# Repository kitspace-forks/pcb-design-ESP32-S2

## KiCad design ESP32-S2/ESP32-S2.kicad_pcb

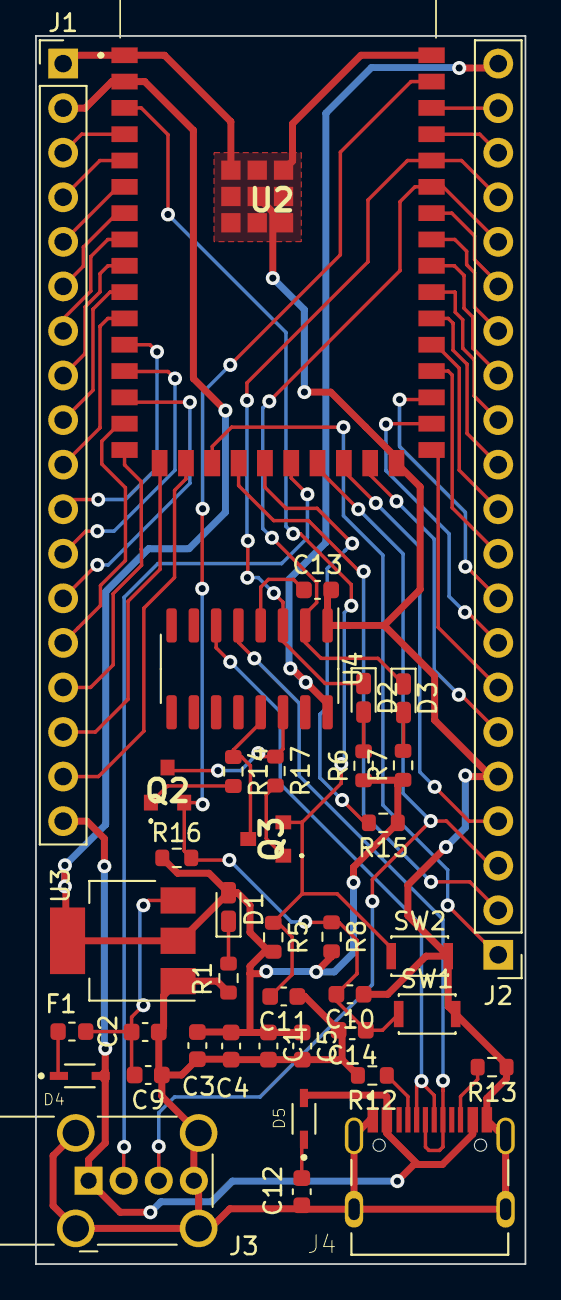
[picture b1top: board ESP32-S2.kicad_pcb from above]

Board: 2 copper layers, 27.9 x 70.0 mm, 39 parts (0 on the bottom side), 57 nets.

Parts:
C1, C4, C9, C10, C11, C12: 0.1uF; C_0603_1608Metric
C2, C5: 10uF; C_0603_1608Metric
C3: 22uF; C_0603_1608Metric
C13: 10nF; C_0603_1608Metric
C14: 1uF; C_0603_1608Metric
D1, D2, D3: LED; LED_0603_1608Metric_Castellated
D4, D5: BAT760-7; SOD2513X120N
F1: Polyfuse_Small; Fuse_0603_1608Metric
J1: Conn_01x18_Male; PinHeader_1x18_P2.54mm_Vertical
J2: Conn_01x21_Male; PinHeader_1x21_P2.54mm_Vertical
J3: USB_A; USB_A_Wuerth_614004134726_Horizontal
J4: TYPE-C-31-M-12; HRO_TYPE-C-31-M-12
Q2, Q3: L8050QLT1G
R1, R6, R7: 1k; R_0603_1608Metric
R5, R8, R14, R15, R16, R17: 10K; R_0603_1608Metric
R12, R13: 5.1K; R_0603_1608Metric
SW1: EN/RESET; SW_SPST_CK_KXT3
SW2: BOOT/SELECT; SW_SPST_CK_KXT3
U2: ESP32-S2-WROOM-ESP32-S2-WROOM; ESP32S2WROOMM22S2H3200PH3Q0
U3: AMS1117-3.3; SOT-223-3_TabPin2
U4: CH340C; SOIC-16_3.9x9.9mm_P1.27mm

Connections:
+3V3: C1.1, C3.1, C4.2, C5.1, D1.2, J1.2, R5.2, R6.1, R7.1, R8.2, R15.1, R16.1, U2.2, U3.2
/CC1: J4.A5, R12.1
/CC2: J4.B5, R13.1
/CHIP_PU: C10.2, C14.1, Q2.2, R8.1, R16.2, SW1.1, U2.41
/DN1: J4.A7, J4.B7, U4.6
/DP1: J4.A6, J4.B6, U4.5
/GPIO0: C11.2, Q3.2, R5.1, SW2.1, U2.3
/GPIO1: J1.3, U2.4
/GPIO2: J1.4, U2.5
/GPIO3: J1.5, U2.6
/GPIO4: J1.6, U2.7
/GPIO5: J1.7, U2.8
/GPIO6: J1.8, U2.9
/GPIO7: J1.9, U2.10
/GPIO8: J1.10, U2.11
/GPIO9: J1.11, U2.12
/GPIO10: J1.12, U2.13
/GPIO11: J1.13, U2.14
/GPIO12: J1.14, U2.15
/GPIO13: J1.15, U2.16
/GPIO14: J1.16, U2.17
/GPIO15: J1.17, U2.18
/GPIO16: J2.1, U2.19
/GPIO17: J2.2, U2.20
/GPIO18: R15.2, U2.21
/GPIO19: J3.2, U2.22
/GPIO20: J2.3, J3.3, U2.23
/GPIO21: J2.4, U2.24
/GPIO26: J2.6, U2.25
/GPIO33: J2.7, U2.27
/GPIO34: J2.8, U2.28
/GPIO35: J2.9, U2.29
/GPIO36: J2.10, U2.30
/GPIO37: J2.11, U2.31
/GPIO38: J2.12, U2.32
/GPIO39: J2.13, U2.33
/GPIO42: J2.16, U2.36
/GPIO45: J2.19, U2.39
/GPIO46: J2.20, U2.40
/RXD0: D2.1, J2.18, U2.38, U4.3
/SCL: J2.14, U2.34
/SDA: J2.15, U2.35
/TXD0: D3.1, J2.17, U2.37, U4.2
/VBUS: D4.A, D5.A, J1.18, J3.1, J4.A4B9, J4.B4A9
/VI: C2.1, C9.2, F1.1, U3.3
/VI2: C12.1, D5.C
/~DTR: Q3.3, R14.1, U4.13
/~RTS: Q2.3, R17.1, U4.14
GND: C1.2, C2.2, C3.2, C4.1, C5.2, C9.1, C10.1, C11.1, C12.2, C13.2, C14.2, J1.1, J2.5, J3.4, J3.5, J4.A1B12, J4.B1A12, J4.S1, J4.S2, J4.S3, J4.S4, R1.2, R12.2, R13.2, SW1.2, SW2.2, U2.1, U2.26, U2.42, U2.43, U2.44, U2.45, U2.46, U2.47, U2.48, U2.49, U2.50, U2.51, U3.1, U4.1
unnamed: C13.1, U4.4
unnamed: D1.1, R1.1
unnamed: D2.2, R6.2
unnamed: D3.2, R7.2
unnamed: D4.C, F1.2
unnamed: Q2.1, R14.2
unnamed: Q3.1, R17.2
VCC: J2.21, U4.16

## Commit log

2021-02-16 routing done- v.1
